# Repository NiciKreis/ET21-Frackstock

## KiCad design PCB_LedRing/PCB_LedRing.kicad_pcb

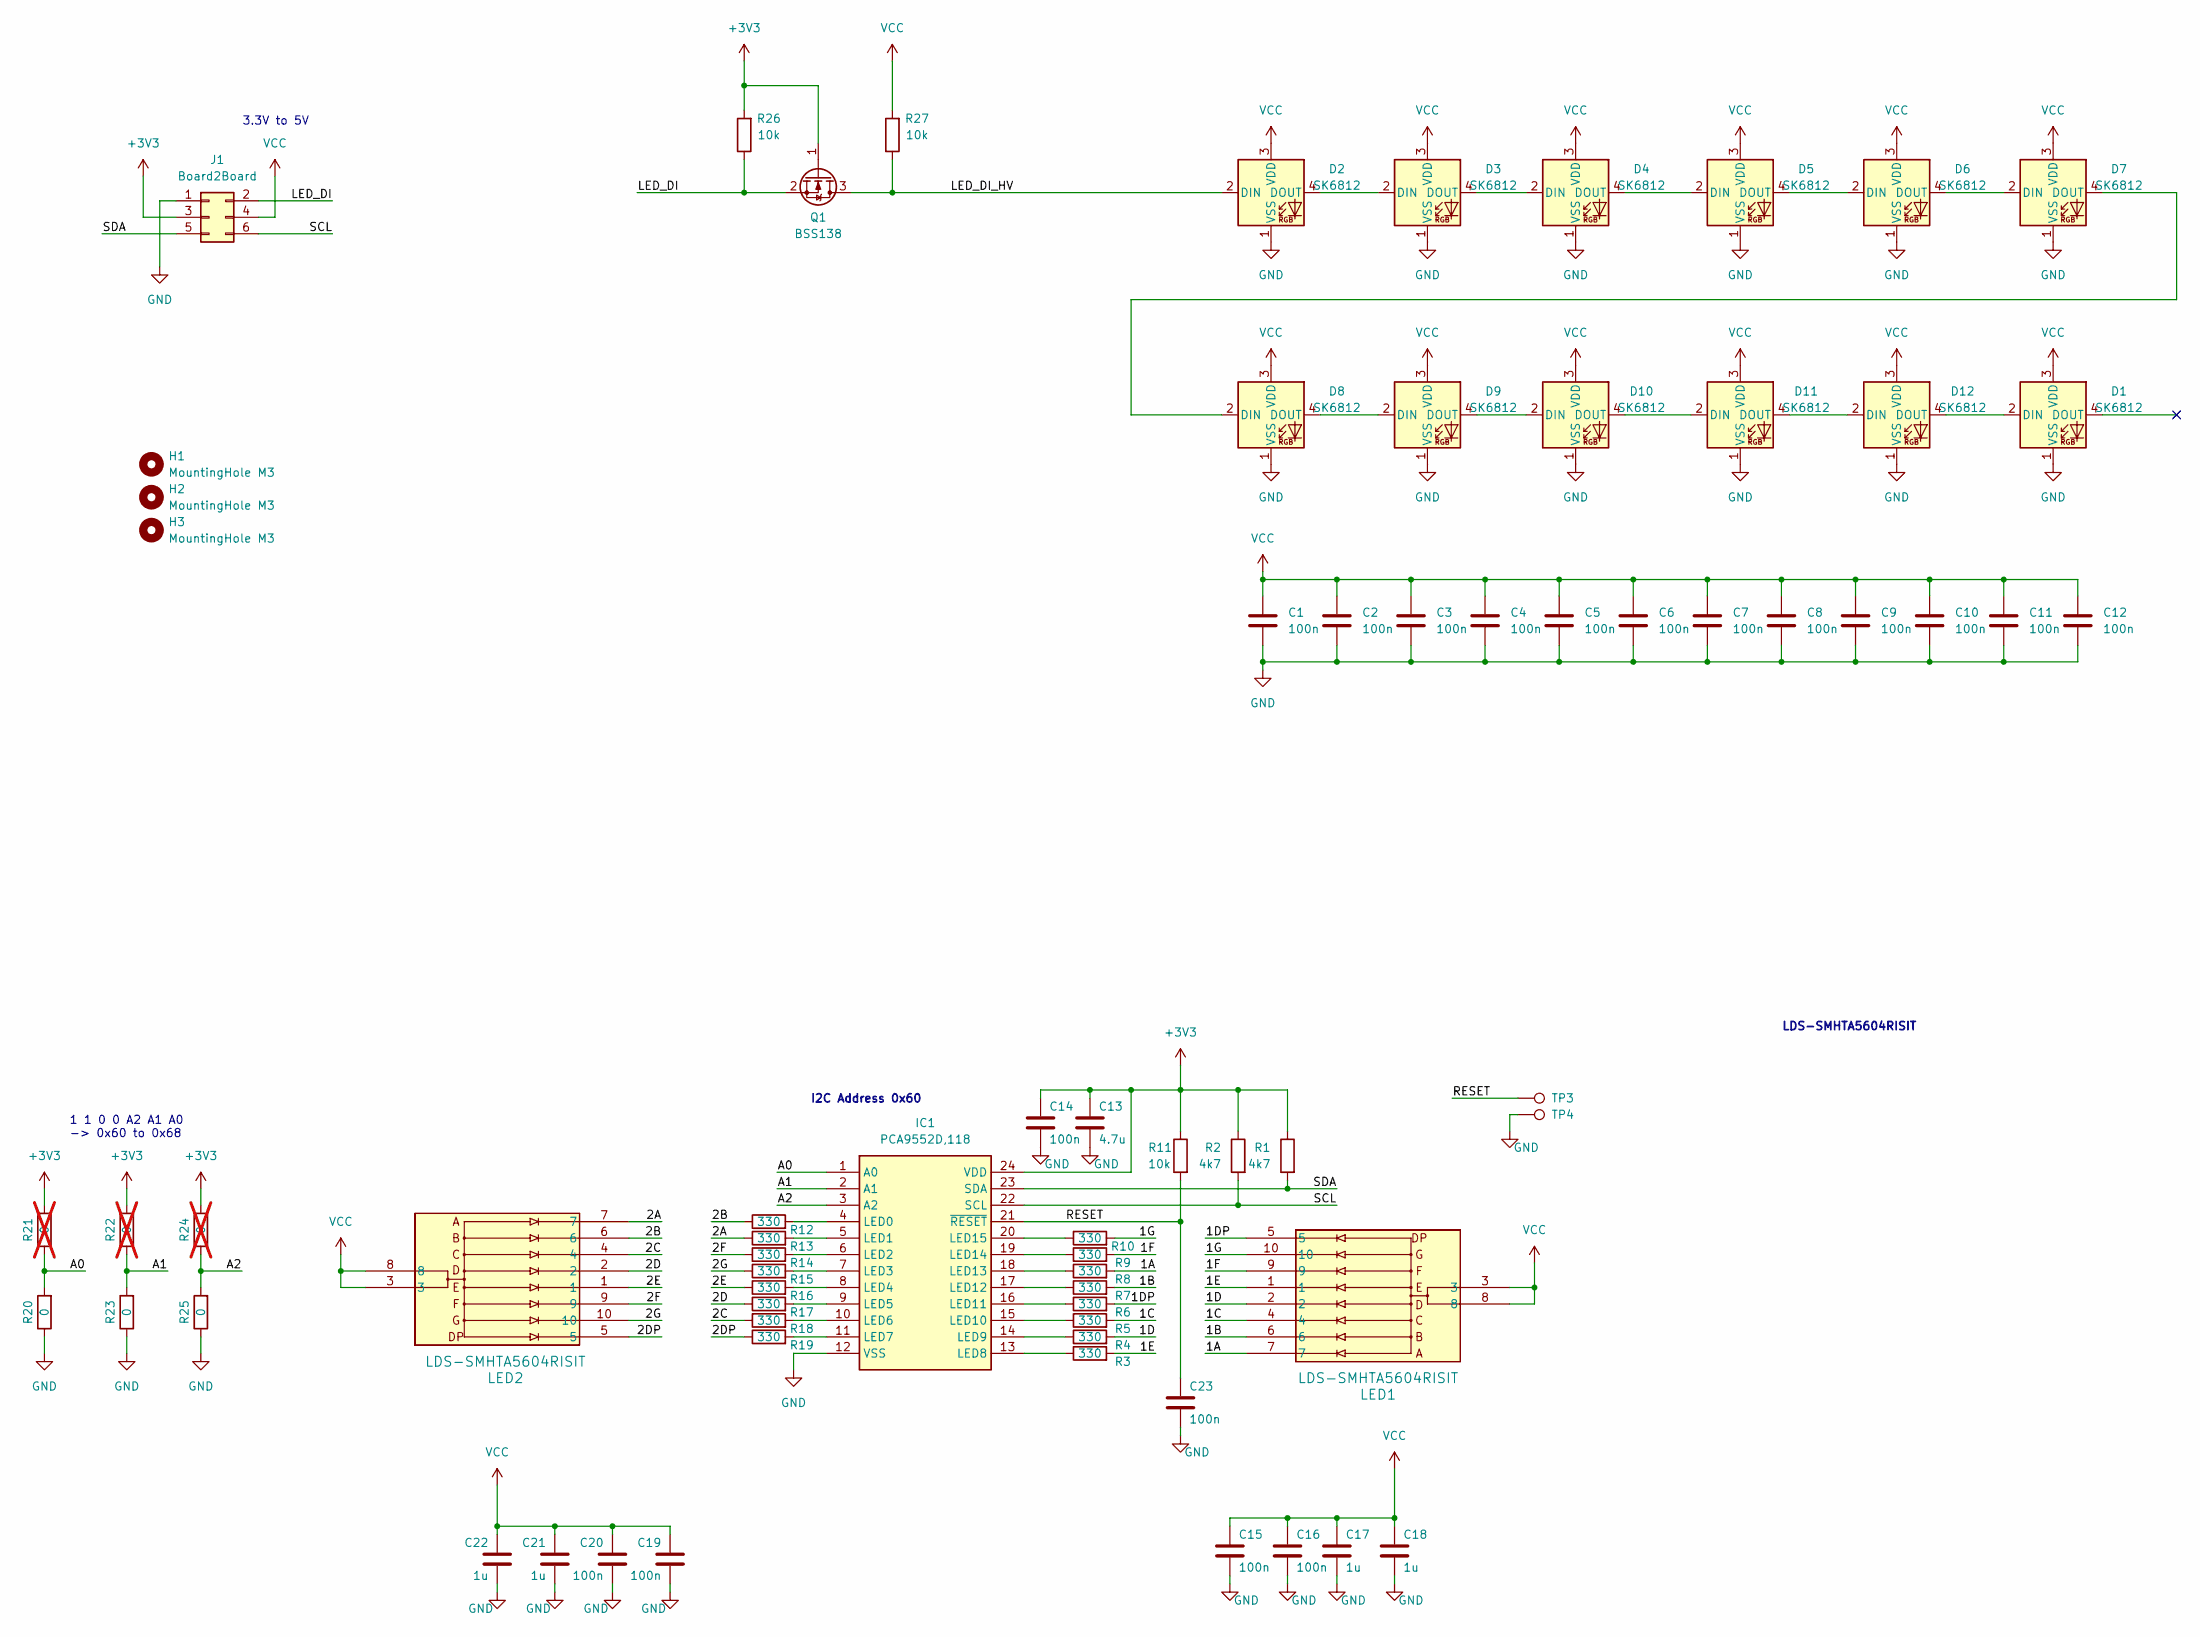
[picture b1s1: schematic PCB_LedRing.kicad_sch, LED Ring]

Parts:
C1, C2, C3, C4, C5, C6, C7, C8, C9, C10, C11, C12, C14, C15, C16, C19, C20, C23: 100n; C_0603_1608Metric_Pad1.08x0.95mm_HandSolder
C13: 4.7u; C_0603_1608Metric_Pad1.08x0.95mm_HandSolder
C17, C18, C21, C22: 1u; C_0603_1608Metric_Pad1.08x0.95mm_HandSolder
D1, D2, D3, D4, D5, D6, D7, D8, D9, D10, D11, D12: SK6812; LED_SK6812_PLCC4_5.0x5.0mm_P3.2mm
H1, H2, H3: MountingHole M3; MountingHole_3.2mm_M3
IC1: PCA9552D,118; SOIC127P1032X265-24N; Mouser Part Number 771-PCA9552D-T
J1: Board2Board; PinHeader_2x03_P2.54mm_Vertical_SMD; Mouser 649-1012938390602BLF
LED1, LED2: LDS-SMHTA5604RISIT; LDS-SMHTA5604RISIT_LUM; Mouser 696-LDSSMHTA5604RISI
Q1: BSS138; SOT-23; Mouser 512-BSS138
R1, R2: 4k7; R_0603_1608Metric_Pad0.98x0.95mm_HandSolder
R3, R4, R5, R6, R7, R8, R9, R10, R12, R13, R14, R15, R16, R17, R18, R19: 330; R_0603_1608Metric_Pad0.98x0.95mm_HandSolder
R11, R26, R27: 10k; R_0603_1608Metric_Pad0.98x0.95mm_HandSolder
R20, R23, R25: 0; R_0603_1608Metric_Pad0.98x0.95mm_HandSolder
R21, R22, R24: 0; R_0603_1608Metric_Pad0.98x0.95mm_HandSolder; not fitted
TP3, TP4: TestPoint; TestPoint_Pad_D3.0mm

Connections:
+3V3: C13.1, C14.1, IC1.24 (VDD), J1.3, Q1.1 (G), R1.1, R2.1, R11.1, R21.2, R22.2, R24.2, R26.2
/1A: LED1.7, R8.2
/1B: LED1.6, R7.2
/1C: LED1.4, R5.2
/1D: LED1.2, R4.2
/1DP: LED1.5, R6.2
/1E: LED1.1, R3.2
/1F: LED1.9, R9.2
/1G: LED1.10, R10.2
/2A: LED2.7, R13.1
/2B: LED2.6, R12.1
/2C: LED2.4, R18.1
/2D: LED2.2, R17.1
/2DP: LED2.5, R19.1
/2E: LED2.1, R16.1
/2F: LED2.9, R14.1
/2G: LED2.10, R15.1
/A0: IC1.1 (A0), R20.2, R21.1
/A1: IC1.2 (A1), R22.1, R23.2
/A2: IC1.3 (A2), R24.1, R25.2
/LED_DI: J1.2, Q1.2 (S), R26.1
/LED_DI_HV: D2.2 (DIN), Q1.3 (D), R27.1
/RESET: C23.1, IC1.21 (~RESET), R11.2, TP3.1
/SCL: IC1.22 (SCL), J1.6, R2.2
/SDA: IC1.23 (SDA), J1.5, R1.2
GND: C1.2, C2.2, C3.2, C4.2, C5.2, C6.2, C7.2, C8.2, C9.2, C10.2, C11.2, C12.2, C13.2, C14.2, C15.2, C16.2, C17.2, C18.2, C19.2, C20.2, C21.2, C22.2, C23.2, D1.1 (VSS), D2.1 (VSS), D3.1 (VSS), D4.1 (VSS), D5.1 (VSS), D6.1 (VSS), D7.1 (VSS), D8.1 (VSS), D9.1 (VSS), D10.1 (VSS), D11.1 (VSS), D12.1 (VSS), IC1.12 (VSS), J1.1, R20.1, R23.1, R25.1, TP4.1
unnamed: D1.2 (DIN), D12.4 (DOUT)
unnamed: D2.4 (DOUT), D3.2 (DIN)
unnamed: D3.4 (DOUT), D4.2 (DIN)
unnamed: D4.4 (DOUT), D5.2 (DIN)
unnamed: D5.4 (DOUT), D6.2 (DIN)
unnamed: D6.4 (DOUT), D7.2 (DIN)
unnamed: D7.4 (DOUT), D8.2 (DIN)
unnamed: D8.4 (DOUT), D9.2 (DIN)
unnamed: D9.4 (DOUT), D10.2 (DIN)
unnamed: D10.4 (DOUT), D11.2 (DIN)
unnamed: D11.4 (DOUT), D12.2 (DIN)
unnamed: IC1.4 (LED0), R12.2
unnamed: IC1.5 (LED1), R13.2
unnamed: IC1.6 (LED2), R14.2
unnamed: IC1.7 (LED3), R15.2
unnamed: IC1.8 (LED4), R16.2
unnamed: IC1.9 (LED5), R17.2
unnamed: IC1.10 (LED6), R18.2
unnamed: IC1.11 (LED7), R19.2
unnamed: IC1.13 (LED8), R3.1
unnamed: IC1.14 (LED9), R4.1
unnamed: IC1.15 (LED10), R5.1
unnamed: IC1.16 (LED11), R6.1
unnamed: IC1.17 (LED12), R7.1
unnamed: IC1.18 (LED13), R8.1
unnamed: IC1.19 (LED14), R9.1
unnamed: IC1.20 (LED15), R10.1
VCC: C1.1, C2.1, C3.1, C4.1, C5.1, C6.1, C7.1, C8.1, C9.1, C10.1, C11.1, C12.1, C15.1, C16.1, C17.1, C18.1, C19.1, C20.1, C21.1, C22.1, D1.3 (VDD), D2.3 (VDD), D3.3 (VDD), D4.3 (VDD), D5.3 (VDD), D6.3 (VDD), D7.3 (VDD), D8.3 (VDD), D9.3 (VDD), D10.3 (VDD), D11.3 (VDD), D12.3 (VDD), J1.4, LED1.3, LED1.8, LED2.3, LED2.8, R27.2

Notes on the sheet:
1 1 0 0 A2 A1 A0 -> 0x60 to 0x68
I2C Address 0x60
3.3V to 5V
LDS-SMHTA5604RISIT

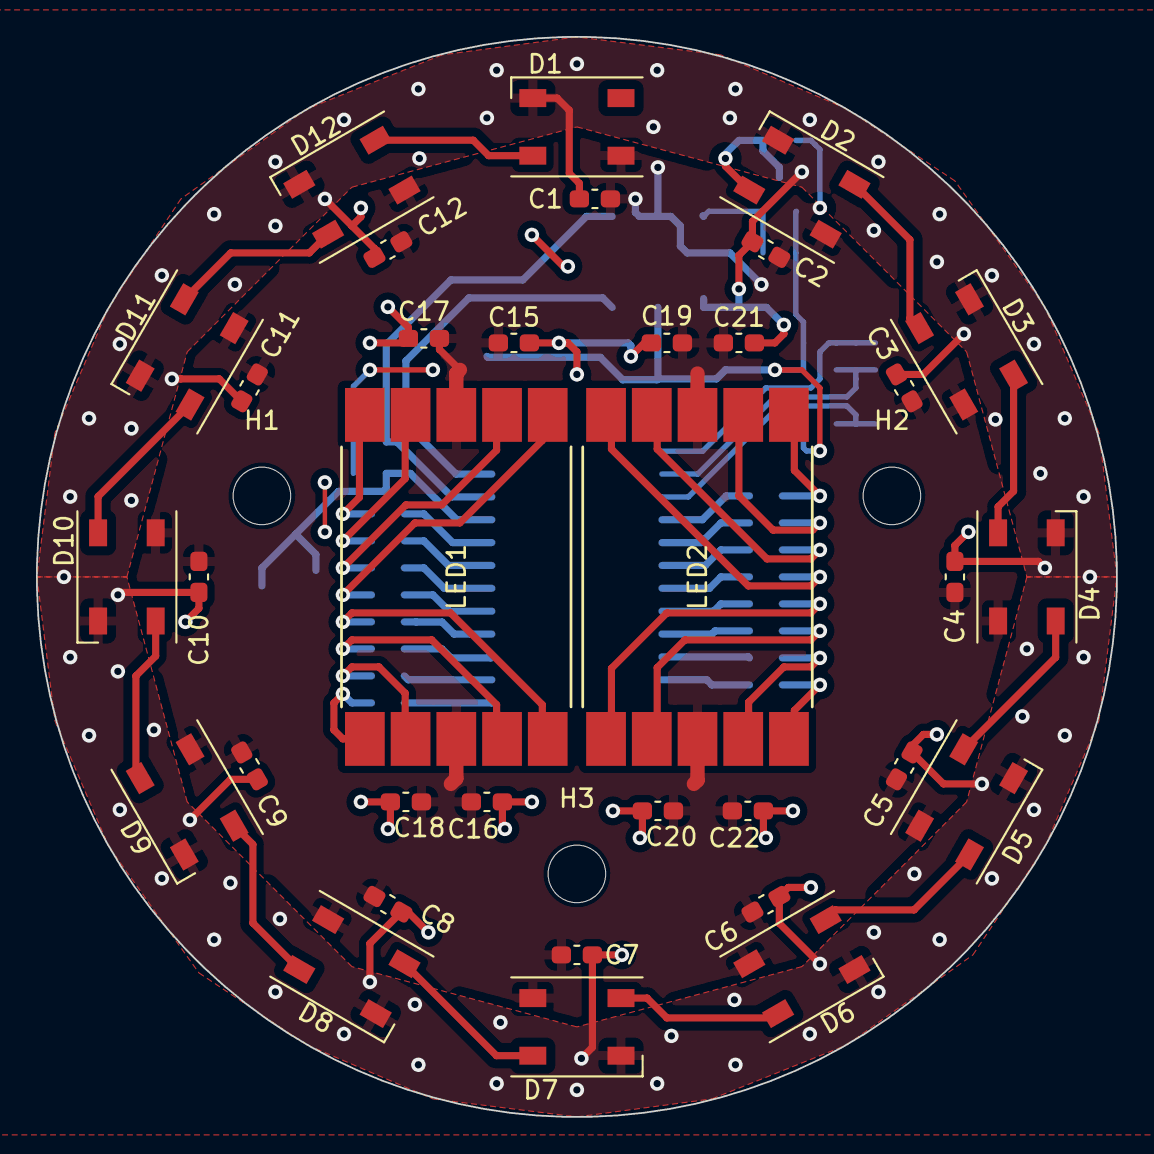
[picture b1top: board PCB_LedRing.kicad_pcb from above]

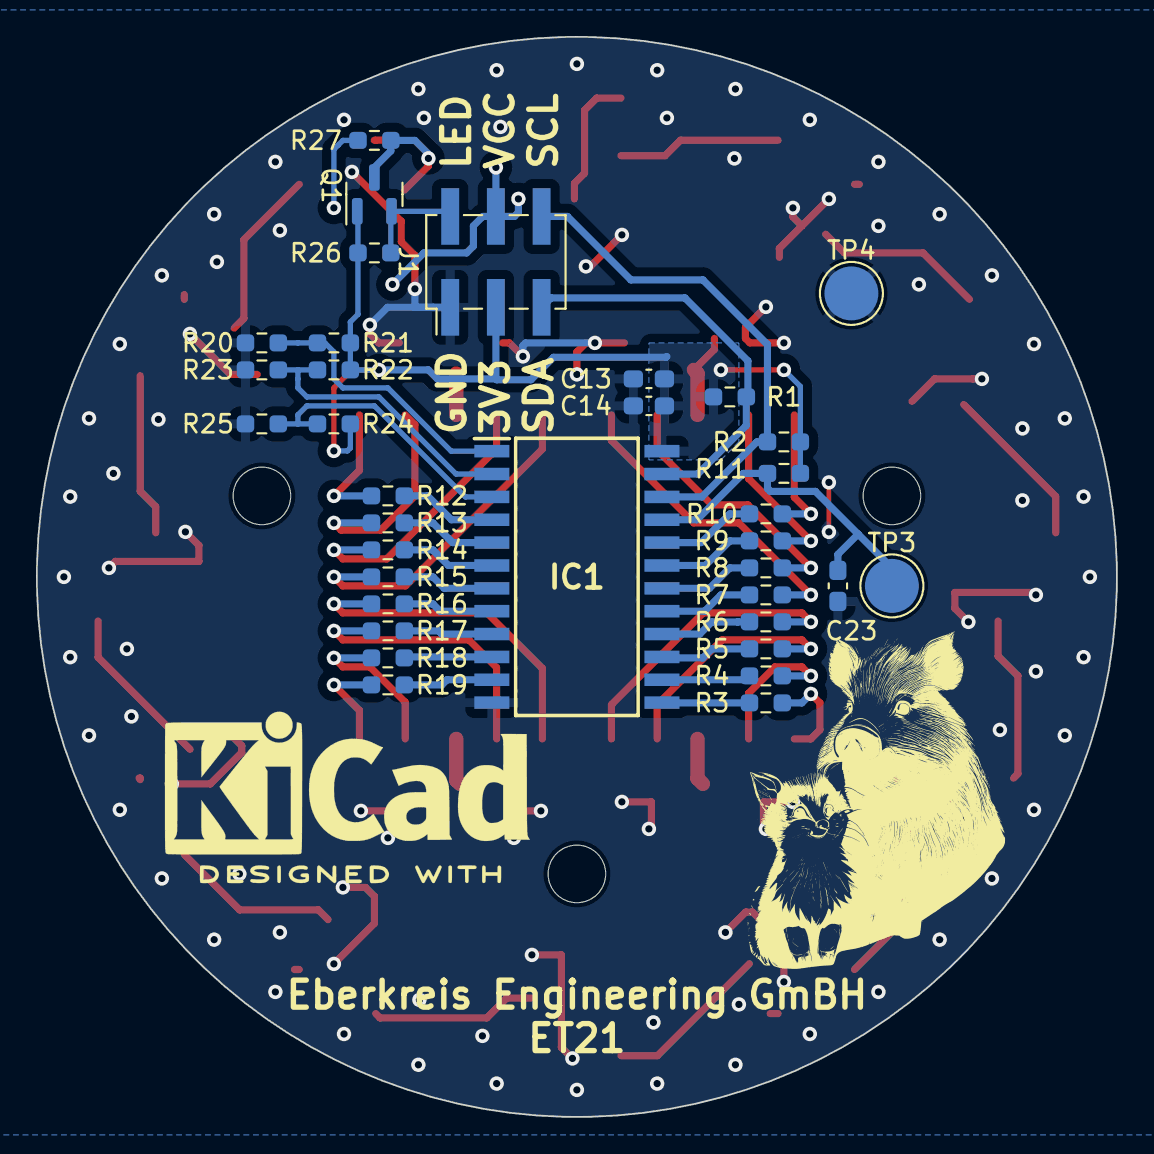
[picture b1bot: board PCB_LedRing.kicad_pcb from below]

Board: 2 copper layers, 60.0 x 60.0 mm, 72 parts (35 on the bottom side), 54 nets.

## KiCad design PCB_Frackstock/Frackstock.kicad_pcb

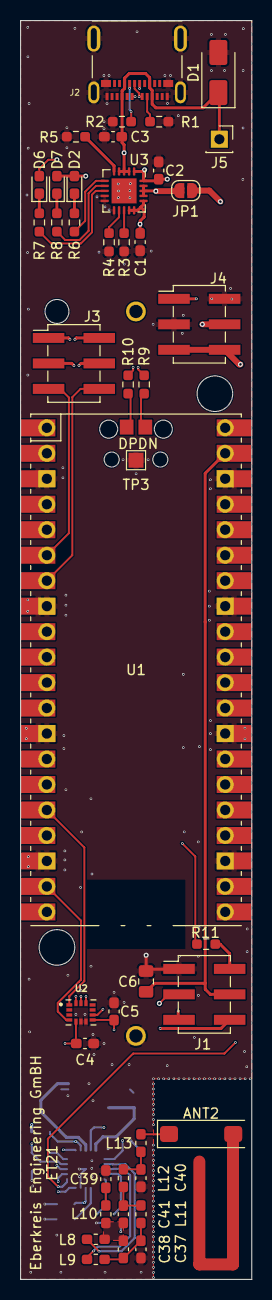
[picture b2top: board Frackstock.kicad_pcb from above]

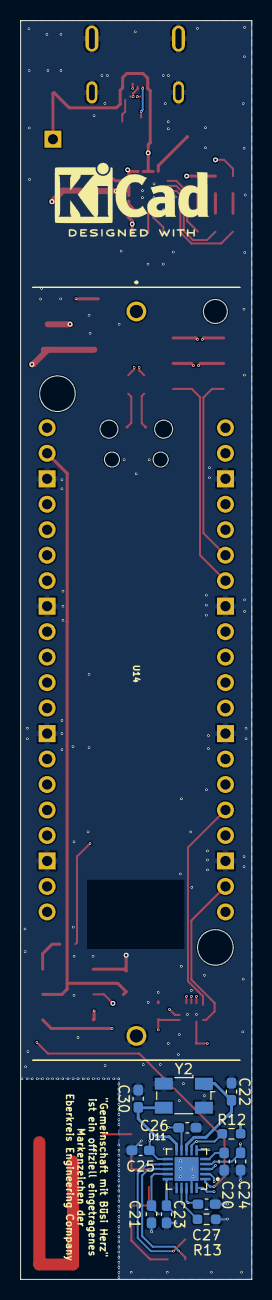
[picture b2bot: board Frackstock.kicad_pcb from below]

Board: 4 copper layers, 23.0 x 125.5 mm, 59 parts (14 on the bottom side), 56 nets.

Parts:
ANT2: W3000
C1, C2: 4.7u; C_0603_1608Metric_Pad1.08x0.95mm_HandSolder
C3: 10u; C_0603_1608Metric_Pad1.08x0.95mm_HandSolder
C4, C5, C20, C21, C23, C24, C25, C26, C27: 100n; C_0603_1608Metric_Pad1.08x0.95mm_HandSolder
C6: 330u; C_0805_2012Metric_Pad1.18x1.45mm_HandSolder
C22, C30: 20p; C_0603_1608Metric_Pad1.08x0.95mm_HandSolder
C37, C41: 1.5pF; C_0603_1608Metric_Pad1.08x0.95mm_HandSolder
C38: 1p; C_0603_1608Metric_Pad1.08x0.95mm_HandSolder
C39: 100pF; C_0603_1608Metric_Pad1.08x0.95mm_HandSolder
C40: 3.3pF; C_0603_1608Metric_Pad1.08x0.95mm_HandSolder
D1: SMAJ5.0A; D_SMA
D2: Blau; LED_0603_1608Metric_Pad1.05x0.95mm_HandSolder
D6: Rot; LED_0603_1608Metric_Pad1.05x0.95mm_HandSolder
D7: Grün; LED_0603_1608Metric_Pad1.05x0.95mm_HandSolder
J1, J3, J4: Conn_02x03_Pin; PinHeader_2x03_P2.54mm_Vertical_SMD_kleiner
J2: 105450-0101; MOLEX_105450-0101
J5: VBUS; PinSocket_1x01_P2.54mm_Vertical
JP1: SolderJumper_2_Open; SolderJumper-2_P1.3mm_Open_RoundedPad1.0x1.5mm
L8, L9, L12, L13: 12nH; L_0603_1608Metric_Pad1.05x0.95mm_HandSolder
L10, L11: 18nH; L_0603_1608Metric_Pad1.05x0.95mm_HandSolder
R1, R2: 5.1k; R_0603_1608Metric_Pad0.98x0.95mm_HandSolder
R3: 2k; R_0603_1608Metric_Pad0.98x0.95mm_HandSolder
R4: 8.2k; R_0603_1608Metric_Pad0.98x0.95mm_HandSolder
R5, R12: 10k; R_0603_1608Metric_Pad0.98x0.95mm_HandSolder
R6, R8: 390; R_0603_1608Metric_Pad0.98x0.95mm_HandSolder
R7: 430; R_0603_1608Metric_Pad0.98x0.95mm_HandSolder
R9, R10: 27; R_0603_1608Metric_Pad0.98x0.95mm_HandSolder
R11: 470; R_0603_1608Metric_Pad0.98x0.95mm_HandSolder
R13: 56k; R_0603_1608Metric_Pad0.98x0.95mm_HandSolder
TP1, TP2: TestPoint_Alt; TestPoint_Pad_1.5x1.5mm_small
TP3: TestPoint_Alt; TestPoint_Pad_1.5x1.5mm
U1: Pico; RPi_Pico_SMD_ohne_Debug
U2: BMI160; PQFN50P250X300X88-14N
U3: MCP73871-2CC; QFN-20-1EP_4x4mm_P0.5mm_EP2.5x2.5mm
U11: CC1101RGPR; QFN50P400X400X100-21N
U14: 1043; Keystone_1043
Y2: 26MHz; Crystal_SMD_Abracon_ABM3B-4Pin_5.0x3.2mm

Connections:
+3.3V: C4.1, C5.1, C21.1, C23.1, C24.1, C25.1, C26.1, C27.1, J1.3, J4.4, R12.1, U1.36 (3V3), U2.5 (VDDIO), U2.8 (VDD), U11.4 (DVDD), U11.9 (AVDD_9), U11.11 (AVDD_11), U11.14 (AVDD_14), U11.15 (AVDD_15), U11.18 (DGUARD)
BAT_O: C2.1, C6.2, D6.2 (A), J1.4, J4.5, J4.6, U1.39 (VSYS), U3.1 (OUT), U3.20 (OUT)
BAT_P: C1.1, U3.14 (V_{BAT}), U3.15 (V_{BAT}), U3.16 (V_{BAT_SENSE}), U14.1 (+)
COM_CLK: U1.24 (GPIO18), U11.1 (SCLK)
COM_CS: R12.2, U1.22 (GPIO17), U11.7 (CSN)
COM_DO1: U1.26 (GPIO20), U11.6 (GDO(ATEST))
COM_DO2: U1.27 (GPIO21), U11.3 (GDO2)
COM_MISO: U1.21 (GPIO16), U11.2 (SO(GDO1))
COM_MOSI: U1.25 (GPIO19), U11.20 (SI)
DN: J2.A7 (D1-), J2.B7 (D2-), R9.2
DP: J2.A6 (D1+), J2.B6 (D2+), R10.2
GND: ANT2.2 (GND), C1.2, C2.2, C3.2, C4.2, C5.2, C6.1, C20.2, C21.2, C22.2, C23.2, C24.2, C25.2, C26.2, C27.2, C30.2, C37.1, C39.1, C40.1, D1.2 (A), J1.1, J2.A1 (GND1), J2.A12 (GND2), J2.B1 (GND3), J2.B12 (GND4), J2.S1 (SHIELD), J2.S2 (SHIELD__1), J2.S3 (SHIELD__2), J2.S4 (SHIELD__3), J4.2, J4.3, R1.1, R2.1, R3.1, R4.1, R5.1, R13.2, TP3.1, U1.3 (GND), U1.8 (GND), U1.13 (GND), U1.18 (GND), U1.23 (GND), U1.28 (GND), U1.33 (AGND), U1.38 (GND), U2.6 (GNDIO), U2.7 (GND), U3.9 (~TE), U3.10 (V_{SS}), U3.11 (V_{SS}), U3.21 (V_{SS}), U11.16 (GND_16), U11.19 (GND_19), U11.21 (EXP), U14.2 (-), Y2.2, Y2.4
GPIO2: J3.3, U1.4 (GPIO2)
GPIO3: J3.4, U1.5 (GPIO3)
GPIO4: J3.5, U1.6 (GPIO4)
GPIO5: J3.6, U1.7 (GPIO5)
LED_EXT: R11.1, U1.12 (GPIO9)
unnamed: ANT2.1 (FEED), L13.2
unnamed: C37.2, C38.2, L9.2, L11.1
unnamed: C38.1, C41.2, L8.2, L10.1
unnamed: C39.2, L10.2
unnamed: C40.2, L12.2, L13.1
unnamed: C41.1, L11.2, L12.1
unnamed: D2.1 (K), R6.1
unnamed: D6.1 (K), R7.1
unnamed: D7.1 (K), R8.1
unnamed: J1.2, R11.2
unnamed: J2.A5 (CC1), R1.2
unnamed: J2.B5 (CC2), R2.2
unnamed: JP1.1 (A), U1.40 (VBUS)
unnamed: R9.1, TP1.1
unnamed: R10.1, TP2.1
unnamed: R3.2, U3.13 (PROG1)
unnamed: R4.2, U3.12 (PROG3)
unnamed: R7.2, U3.8 (STAT1/~LBO)
unnamed: R8.2, U3.7 (STAT2)
unnamed: R5.2, U3.5 (THERM)
unnamed: R6.2, U3.6 (~PG)
unnamed: C20.1, U11.5 (DCOUPL)
unnamed: R13.1, U11.17 (RBIAS)
RESET: J4.1, U1.30 (RUN)
RF_N: L9.1, U11.13 (RF_N)
RF_P: L8.1, U11.12 (RF_P)
SCL_EXT: J1.6, U1.32 (GPIO27_ADC1)
SDA_EXT: J1.5, U1.31 (GPIO26_ADC0)
SEN_CS: U1.17 (GPIO13), U2.12 (CSB)
SEN_INT1: U1.19 (GPIO14), U2.4 (INT1)
SEN_INT2: U1.20 (GPIO15), U2.9 (INT2)
SEN_MISO: U1.16 (GPIO12), U2.1 (SDO)
SEN_MOSI: U1.15 (GPIO11), U2.14 (SDX)
SEN_SCK: U1.14 (GPIO10), U2.13 (SCX)
UART0_RX: J3.2, U1.2 (GPIO1)
UART0_TX: J3.1, U1.1 (GPIO0)
VBUS: C3.1, D1.1 (K), D2.2 (A), D7.2 (A), J2.A4 (VBUS1), J2.A9 (VBUS2), J2.B4 (VBUS3), J2.B9 (VBUS4), J5.1, JP1.2 (B), U3.2 (VPCC), U3.3 (SEL), U3.4 (PROG2), U3.17 (CE), U3.18 (IN), U3.19 (IN)
XOSC_Q1: C22.1, U11.8 (XOSC_Q1), Y2.1
XOSC_Q2: C30.1, U11.10 (XOSC_Q2), Y2.3

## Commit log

2023-11-22 Start Project
2023-11-24 Battery Management and change parts to 0603
2024-02-14 Schema fertig
2024-02-22 SW-Frackstock test
2024-02-25 Add LED Ring Board
2024-02-25 Wire Digits and LEDs
2024-02-27 LED Board DRC
2024-03-10 Schema_fertig
2024-03-10 Layout Fertig
2024-03-12 Change connector
2024-03-12 Remove DS_Store
2024-03-13 Layout Update
2024-03-13 USB Differenziell
2024-03-21 Update LED ring based on review
2024-03-24 Frackstock-Schema-review1.0
2024-03-24 Schema-review-1
2024-03-28 Add Level Shifter
2024-03-28 Fracstock PCB final commit
    DRC check, PCB review done, ready to order
2024-03-28 Frackstock Gerber added
2024-03-28 LED Ring Gerber export
2024-04-03 Add Mouser numbers
2024-04-05 Bauteiländerungen
2024-04-09 Exports
2024-05-19 Create LICENSE
